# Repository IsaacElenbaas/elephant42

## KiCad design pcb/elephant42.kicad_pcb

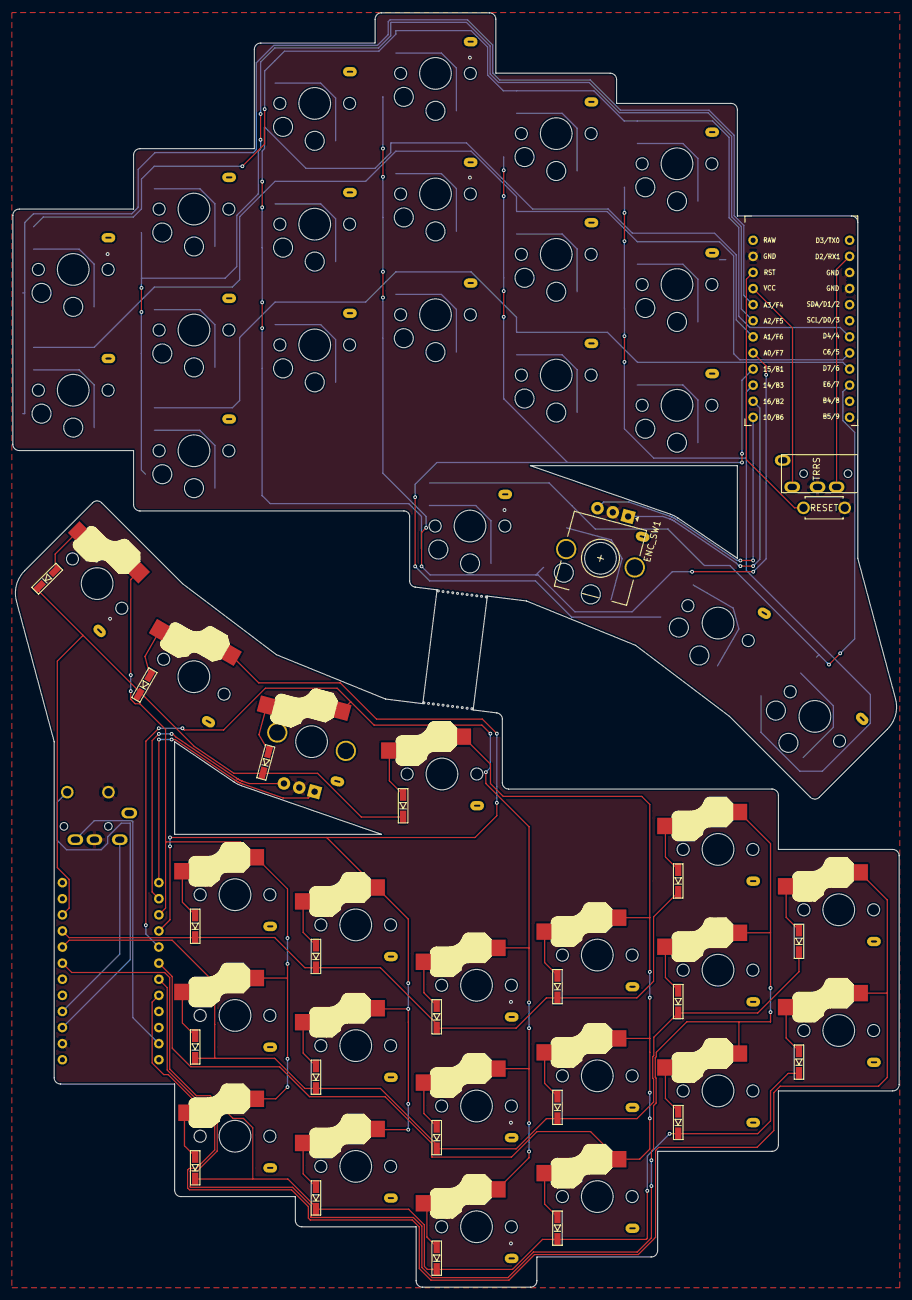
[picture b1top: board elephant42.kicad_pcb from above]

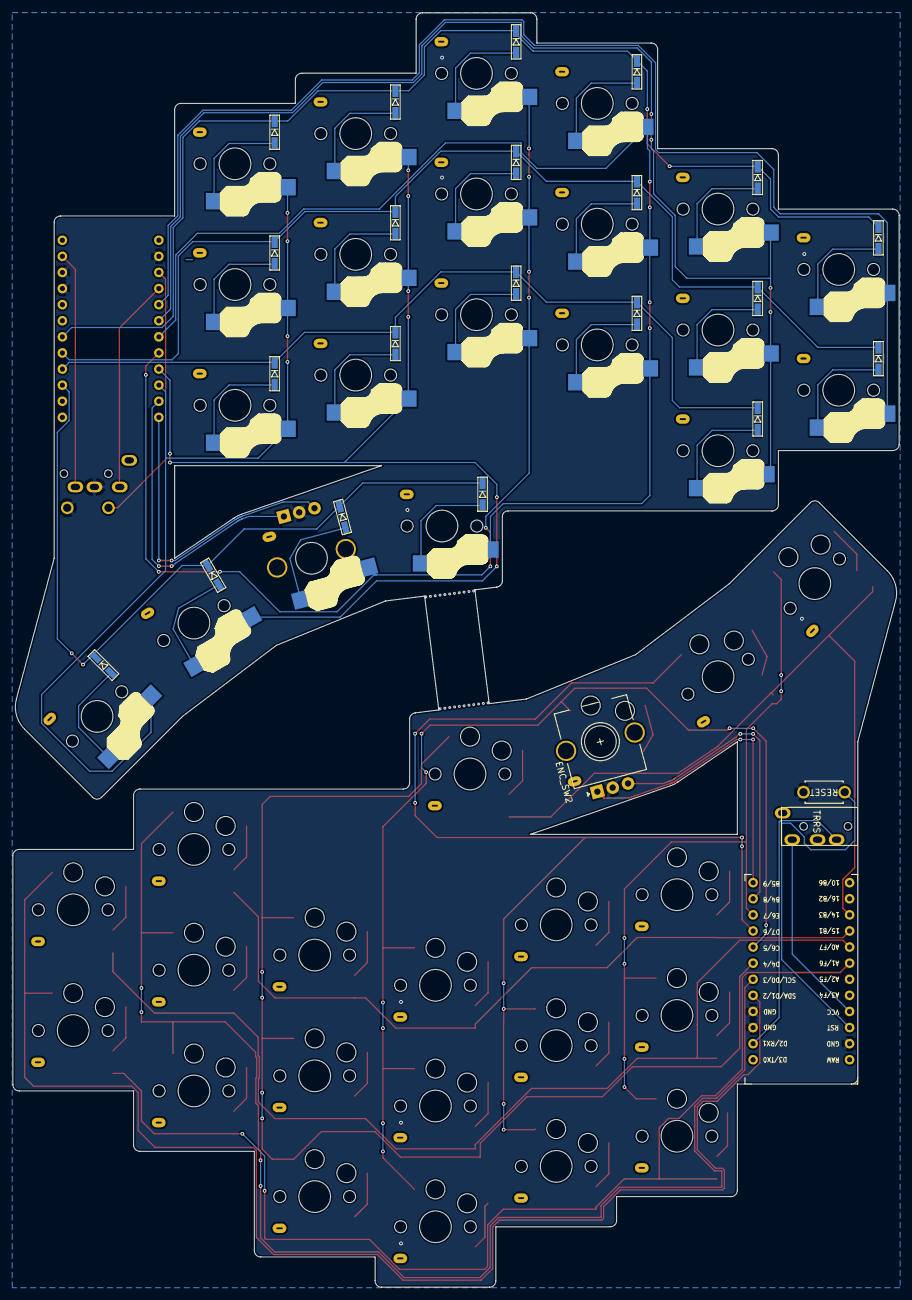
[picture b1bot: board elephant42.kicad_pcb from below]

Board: 2 copper layers, 139.8 x 201.0 mm, 92 parts (46 on the bottom side), 72 nets.

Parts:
D1, D2, D3, D4, D5, D6, D7, D8, D9, D10, D11, D12, D13, D14, D15, D16, D17, D18, D19, D20, D21, D22, D23, D24, D25, D26, D27, D28, D29, D30, D31, D32, D33, D34, D35, D36, D37, D38, D39, D40, D41, D42: D; D3_SMD_v2
ENC_SW1, ENC_SW2: Rotary_Encoder; RotaryEncoder_Alps_EC11E-Switch_Vertical_H20mm_CircularMoun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
J1, J3: MJ-4PP-9; MJ-4PP-9_1side
RESET_SW1, RESET_SW2: SW_PUSH; ResetSW_1side
SW1, SW2, SW3, SW4, SW5, SW6, SW7, SW8, SW9, SW10, SW11, SW12, SW13, SW14, SW15, SW16, SW17, SW18, SW19, SW20, SW21, SW22, SW23, SW24, SW25, SW26, SW27, SW28, SW29, SW30, SW31, SW32, SW33, SW34, SW35, SW36, SW37, SW38, SW39, SW40, SW41, SW42: SW_PUSH; ChocV1_V2_Hotswap
U1, U2: ProMicro; ProMicro_v3

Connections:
GND: ENC_SW1.C, ENC_SW2.C, J1.C, J3.C, RESET_SW1.2, RESET_SW2.2, U1.3, U1.4, U1.23, U2.3, U2.4, U2.23
unnamed: D1.2, SW1.2
unnamed: D2.2, SW2.2
unnamed: D3.2, SW3.2
unnamed: D4.2, SW4.2
unnamed: D5.2, SW5.2
unnamed: D6.2, SW6.2
unnamed: D7.2, SW7.2
unnamed: D8.2, SW8.2
unnamed: D9.2, SW9.2
unnamed: D10.2, SW10.2
unnamed: D11.2, SW11.2
unnamed: D12.2, SW12.2
unnamed: D13.2, SW13.2
unnamed: D14.2, SW14.2
unnamed: D15.2, SW15.2
unnamed: D16.2, SW16.2
unnamed: D17.2, SW17.2
unnamed: D18.2, SW18.2
unnamed: D19.2, SW19.2
unnamed: D20.2, SW20.2
unnamed: D21.2, SW21.2
unnamed: D22.2, SW22.1
unnamed: D23.2, SW23.1
unnamed: D24.2, SW24.1
unnamed: D25.2, SW25.1
unnamed: D26.2, SW26.1
unnamed: D27.2, SW27.1
unnamed: D28.2, SW28.1
unnamed: D29.2, SW29.1
unnamed: D30.2, SW30.1
unnamed: D31.2, SW31.1
unnamed: D32.2, SW32.1
unnamed: D33.2, SW33.1
unnamed: D34.2, SW34.1
unnamed: D35.2, SW35.1
unnamed: D36.2, SW36.1
unnamed: D37.2, SW37.1
unnamed: D38.2, SW38.1
unnamed: D39.2, SW39.1
unnamed: D40.2, SW40.1
unnamed: D41.2, SW41.1
unnamed: D42.2, SW42.1
VCC: J1.D, J3.D, U1.21, U2.21
col0: SW1.1, SW7.1, U1.20
col1: SW2.1, SW8.1, SW13.1, U1.19
col2: SW3.1, SW9.1, SW14.1, SW18.1, U1.18
col3: SW4.1, SW10.1, SW15.1, SW19.1, U1.17
col4: SW5.1, SW11.1, SW16.1, SW20.1, U1.16
col5: SW6.1, SW12.1, SW17.1, SW21.1, U1.15
col6: SW27.2, SW33.2, U2.5
col7: SW26.2, SW32.2, SW38.2, U2.6
col8: SW25.2, SW31.2, SW37.2, SW42.2, U2.7
col9: SW24.2, SW30.2, SW36.2, SW41.2, U2.8
col10: SW23.2, SW29.2, SW35.2, SW40.2, U2.9
col11: SW22.2, SW28.2, SW34.2, SW39.2, U2.10
data_l: J1.B, U1.2
data_r: J3.B, U2.2
enc1: ENC_SW1.A, U1.14
enc2: ENC_SW1.B, U1.13
enc3: ENC_SW2.A, U2.12
enc4: ENC_SW2.B, U2.11
reset_l: RESET_SW1.1, U1.22
reset_r: RESET_SW2.1, U2.22
row0: D1.1, D2.1, D3.1, D4.1, D5.1, D6.1, U1.7
row1: D7.1, D8.1, D9.1, D10.1, D11.1, D12.1, U1.8
row2: D13.1, D14.1, D15.1, D16.1, D17.1, U1.9
row3: D18.1, D19.1, D20.1, D21.1, U1.10
row4: D22.1, D23.1, D24.1, D25.1, D26.1, D27.1, U2.18
row5: D28.1, D29.1, D30.1, D31.1, D32.1, D33.1, U2.17
row6: D34.1, D35.1, D36.1, D37.1, D38.1, U2.16
row7: D39.1, D40.1, D41.1, D42.1, U2.15

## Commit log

2022-02-21 Convert to choc hotswap with encoder
